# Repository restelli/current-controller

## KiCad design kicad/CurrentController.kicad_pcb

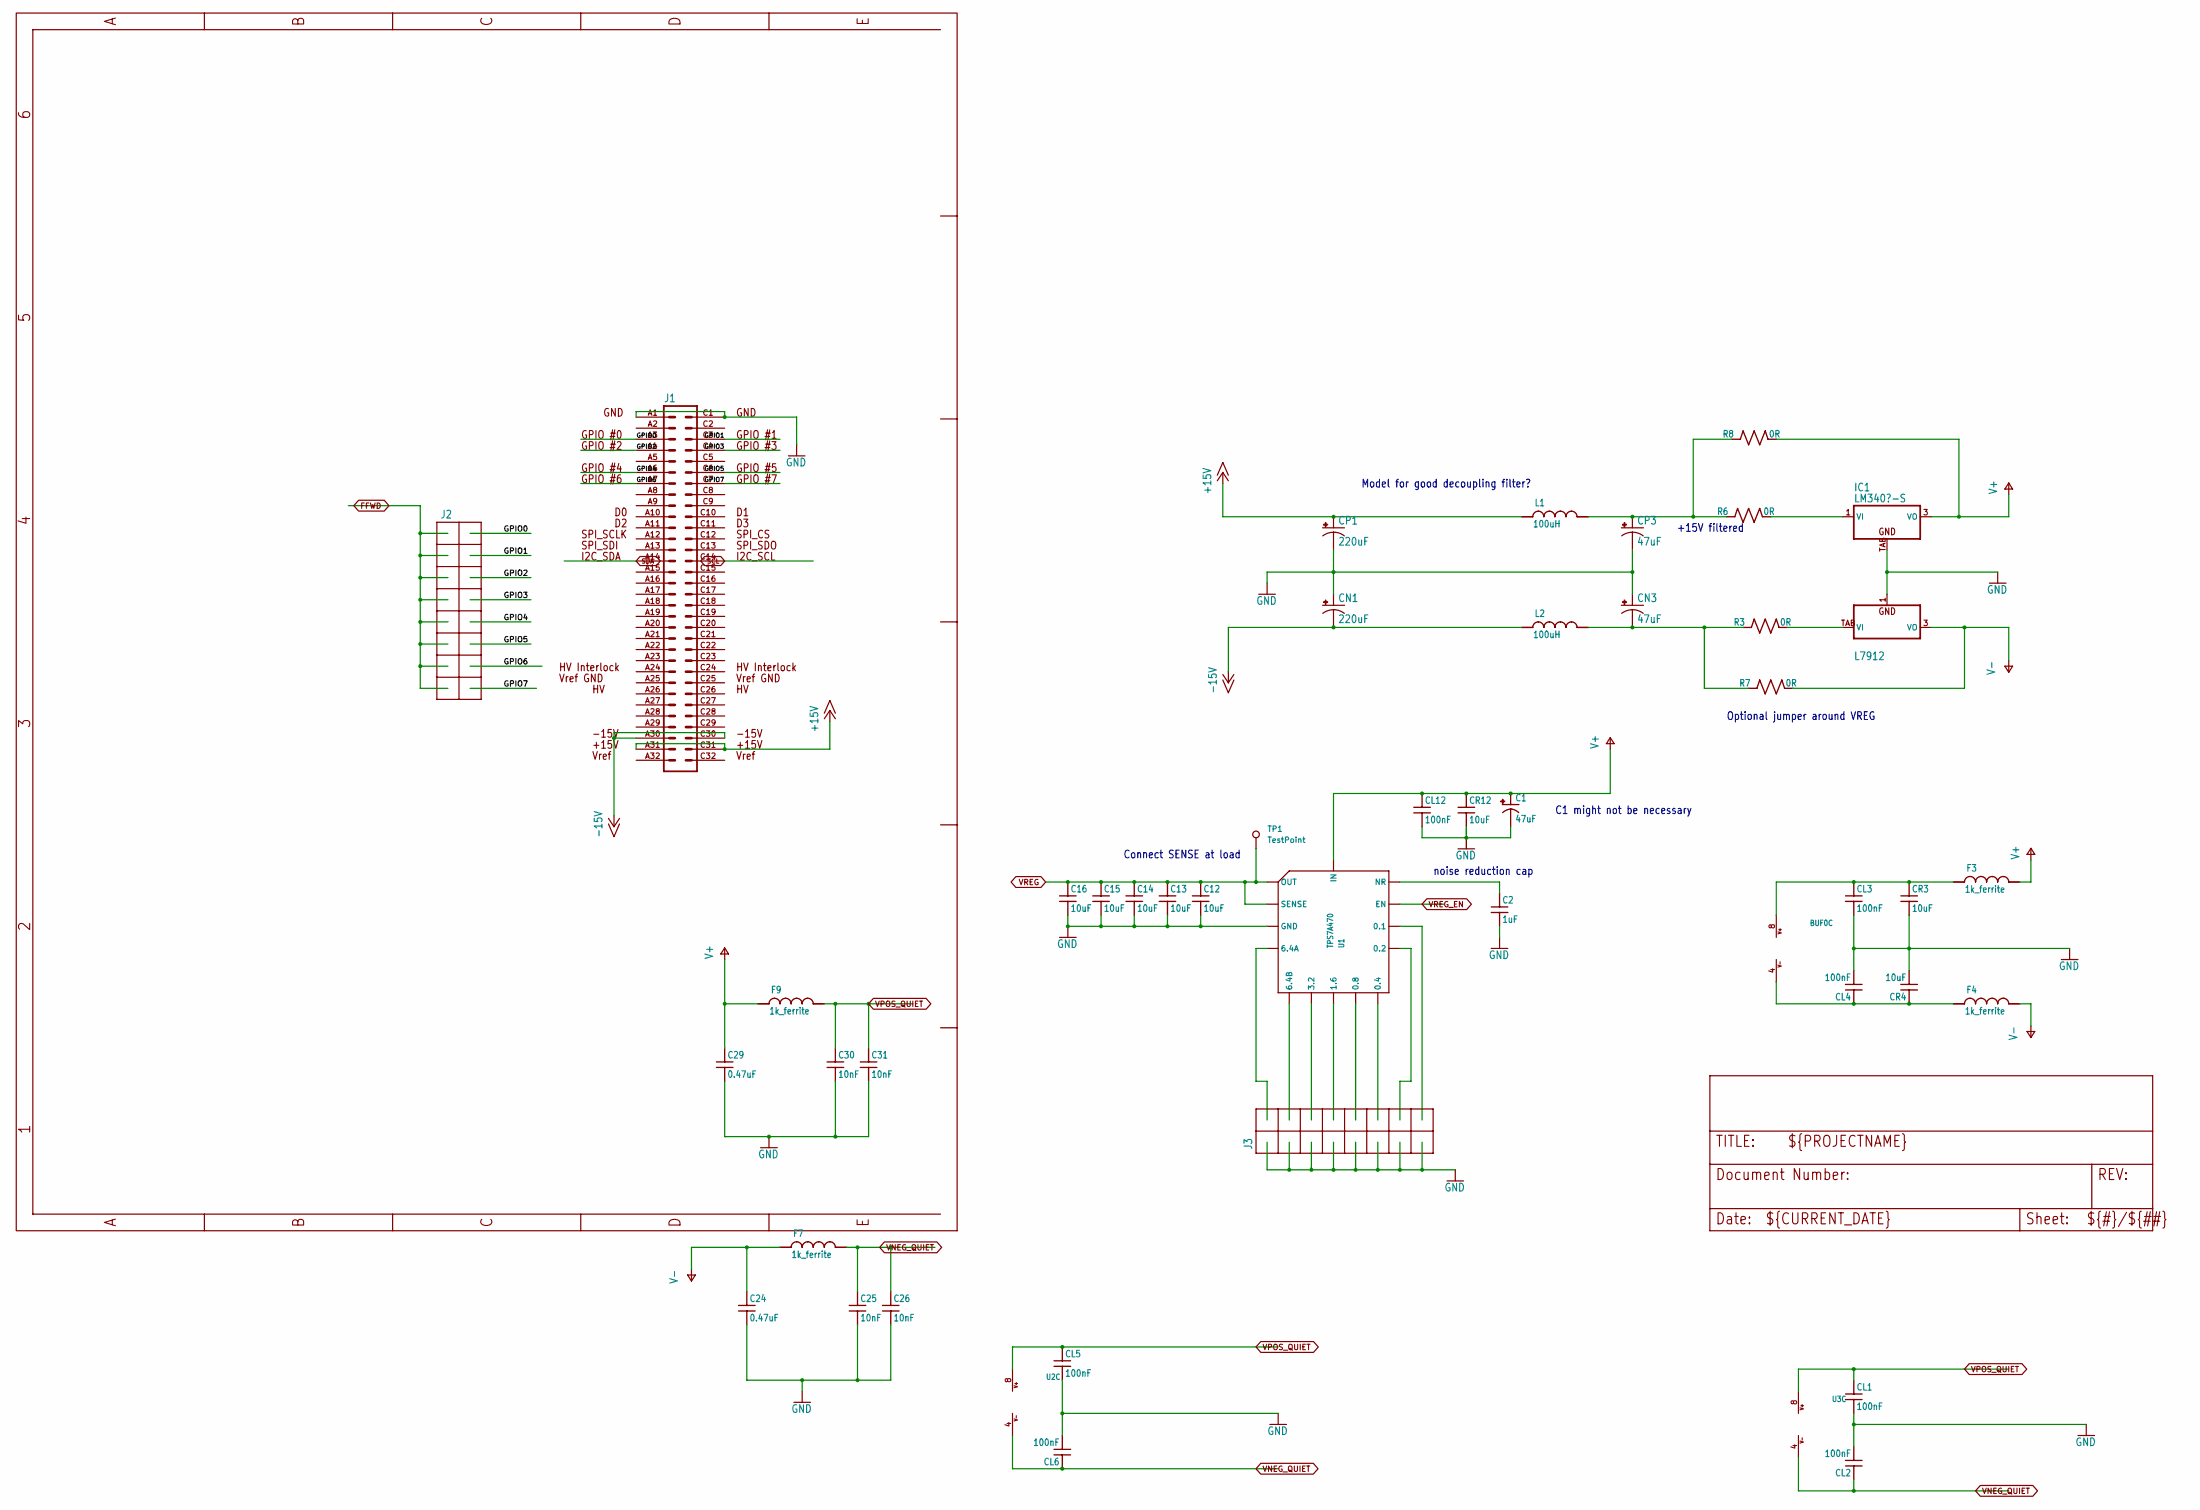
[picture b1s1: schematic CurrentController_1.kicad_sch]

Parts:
BUF0: AD8676; MSOP08; PARTNO AD8676ARMZ
C1: 47uF; C_POL_1206
C2: 1uF; C_MLCC_0603; PARTNO CL10B105KA8NNNC
C12, C13, C14, C15, C16: 10uF; C_MLCC_0805; PARTNO CL21A106KAFN3NE
C24, C29: 0.47uF; C_MLCC_0612; PARTNO LLL31MR71E474MA01L
C25, C26, C30, C31: 10nF; C_MLCC_0306; PARTNO 03063C103KAT2A
CL1, CL2, CL3, CL4, CL5, CL6, CL12: 100nF; C_MLCC_0603; PARTNO C1608X7R1E104K080AA
CN1: 220uF; PANASONIC_F; PARTNO EEE-1VA221UP
CN3: 47uF; CT7343; PARTNO T491D476M025AT
CP1: 220uF; PANASONIC_F; PARTNO EEE-1VA221UP
CP3: 47uF; CT7343; PARTNO T491D476M025AT
CR3, CR4, CR12: 10uF; C_MLCC_0805; PARTNO CL21A106KAFN3NE
F3, F4, F7, F9: 1k_ferrite; L_FERRITE_0603; PARTNO BLM18HG102SN1D
IC1: LM340?-S; TO263-3; PARTNO LM340S-12/NOPB
IC2: L7912; TO223-3; PARTNO MC7912CD2TG
J1: VG64C; VG64-CUTOUT; PARTNO 5650945-5
J2, J3: 2X8_LOW_PROFILE_JUMPER; 2X8_LOW_PROFILE_JUMPER_MATRIX; PARTNO A3B-16PA-2DSA(71)
L1, L2: 100uH; WURTH_1280; PARTNO 74477020
R3, R6, R7, R8: 0R; R_1206; PARTNO ERJ-8GEY0R00V
TP1: TestPoint; TestPoint_Pad_1.0x1.0mm
U1: TPS7A470; S-PVQFN-N20; PARTNO TPS7A4701RGWT
U2, U3: AD8676; MSOP08; PARTNO AD8676ARMZ

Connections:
+15V: CP1.+, J1.A31, J1.C31, L1.P$1 (1)
-15V: CN1.-, J1.A30, J1.C30, L2.P$1 (1)
/CurrentController_1/GPIO0: J1.A3, J2.P$2
/CurrentController_1/GPIO1: J1.C3, J2.P$4
/CurrentController_1/GPIO2: J1.A4, J2.P$6
/CurrentController_1/GPIO3: J1.C4, J2.P$8
/CurrentController_1/GPIO4: J1.A6, J2.P$10
/CurrentController_1/GPIO5: J1.C6, J2.P$12
/CurrentController_1/GPIO6: J1.A7, J2.P$14
/CurrentController_1/GPIO7: J1.C7, J2.P$16
FFWD: J2.P$1, J2.P$3, J2.P$5, J2.P$7, J2.P$9, J2.P$11, J2.P$13, J2.P$15; also elsewhere on the board
GND: C1.P$2 (-), C2.P$2 (2), C12.P$2 (2), C13.P$2 (2), C14.P$2 (2), C15.P$2 (2), C16.P$2 (2), C24.P$2 (2), C25.P$2 (2), C26.P$2 (2), C29.P$2 (2), C30.P$2 (2), C31.P$2 (2), CL1.P$2 (2), CL2.P$2 (2), CL3.P$2 (2), CL4.P$2 (2), CL5.P$2 (2), CL6.P$2 (2), CL12.P$2 (2), CN1.+, CN3.+, CP1.-, CP3.-, CR3.P$2 (2), CR4.P$2 (2), CR12.P$2 (2), IC1.TAB (GND), IC2.1 (GND), J1.A1, J1.C1, J3.P$1, J3.P$3, J3.P$5, J3.P$7, J3.P$9, J3.P$11, J3.P$13, J3.P$15, U1.2 (GND), U1.7 (GND), U1.17 (GND), U1.18 (GND), U1.19 (GND), U1.EXP (GND); also elsewhere on the board
unnamed: BUF0.8 (V+), CL3.P$1 (1), CR3.P$1 (1), F3.P$1 (1)
unnamed: BUF0.4 (V-), CL4.P$1 (1), CR4.P$1 (1), F4.P$1 (1)
unnamed: C2.P$1 (1), U1.14 (NR)
unnamed: IC1.1 (VI), R6.P$2 (2)
unnamed: IC2.TAB (VI), R3.P$2 (2)
unnamed: CP3.+, L1.P$2 (2), R6.P$1 (1), R8.P$1 (1)
unnamed: CN3.-, L2.P$2 (2), R3.P$1 (1), R7.P$1 (1)
unnamed: J3.P$16, U1.12 (0.1)
unnamed: J3.P$14, U1.11 (0.2)
unnamed: J3.P$12, U1.10 (0.4)
unnamed: J3.P$10, U1.9 (0.8)
unnamed: J3.P$8, U1.8 (1.6)
unnamed: J3.P$6, U1.6 (3.2)
unnamed: J3.P$2, U1.4 (6.4A)
unnamed: J3.P$4, U1.5 (6.4B)
SCL: J1.C14; also elsewhere on the board
SDA: J1.A14; also elsewhere on the board
V+: C1.P$1 (+), C29.P$1 (1), CL12.P$1 (1), CR12.P$1 (1), F3.P$2 (2), F9.P$1 (1), IC1.3 (VO), R8.P$2 (2), U1.15 (IN), U1.16 (IN); also elsewhere on the board
V-: C24.P$1 (1), F4.P$2 (2), F7.P$1 (1), IC2.3 (VO), R7.P$2 (2); also elsewhere on the board
VNEG_QUIET: C25.P$1 (1), C26.P$1 (1), CL2.P$1 (1), CL6.P$1 (1), F7.P$2 (2), U2.4 (V-), U3.4 (V-); also elsewhere on the board
VPOS_QUIET: C30.P$1 (1), C31.P$1 (1), CL1.P$1 (1), CL5.P$1 (1), F9.P$2 (2), U2.8 (V+), U3.8 (V+); also elsewhere on the board
VREG: C12.P$1 (1), C13.P$1 (1), C14.P$1 (1), C15.P$1 (1), C16.P$1 (1), TP1.1, U1.1 (OUT), U1.3 (SENSE), U1.20 (OUT); also elsewhere on the board
VREG_EN: U1.13 (EN); also elsewhere on the board

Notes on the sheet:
Optional jumper around VREG
C1 might not be necessary
Model for good decoupling filter?
+15V filtered
Connect SENSE at load
noise reduction cap

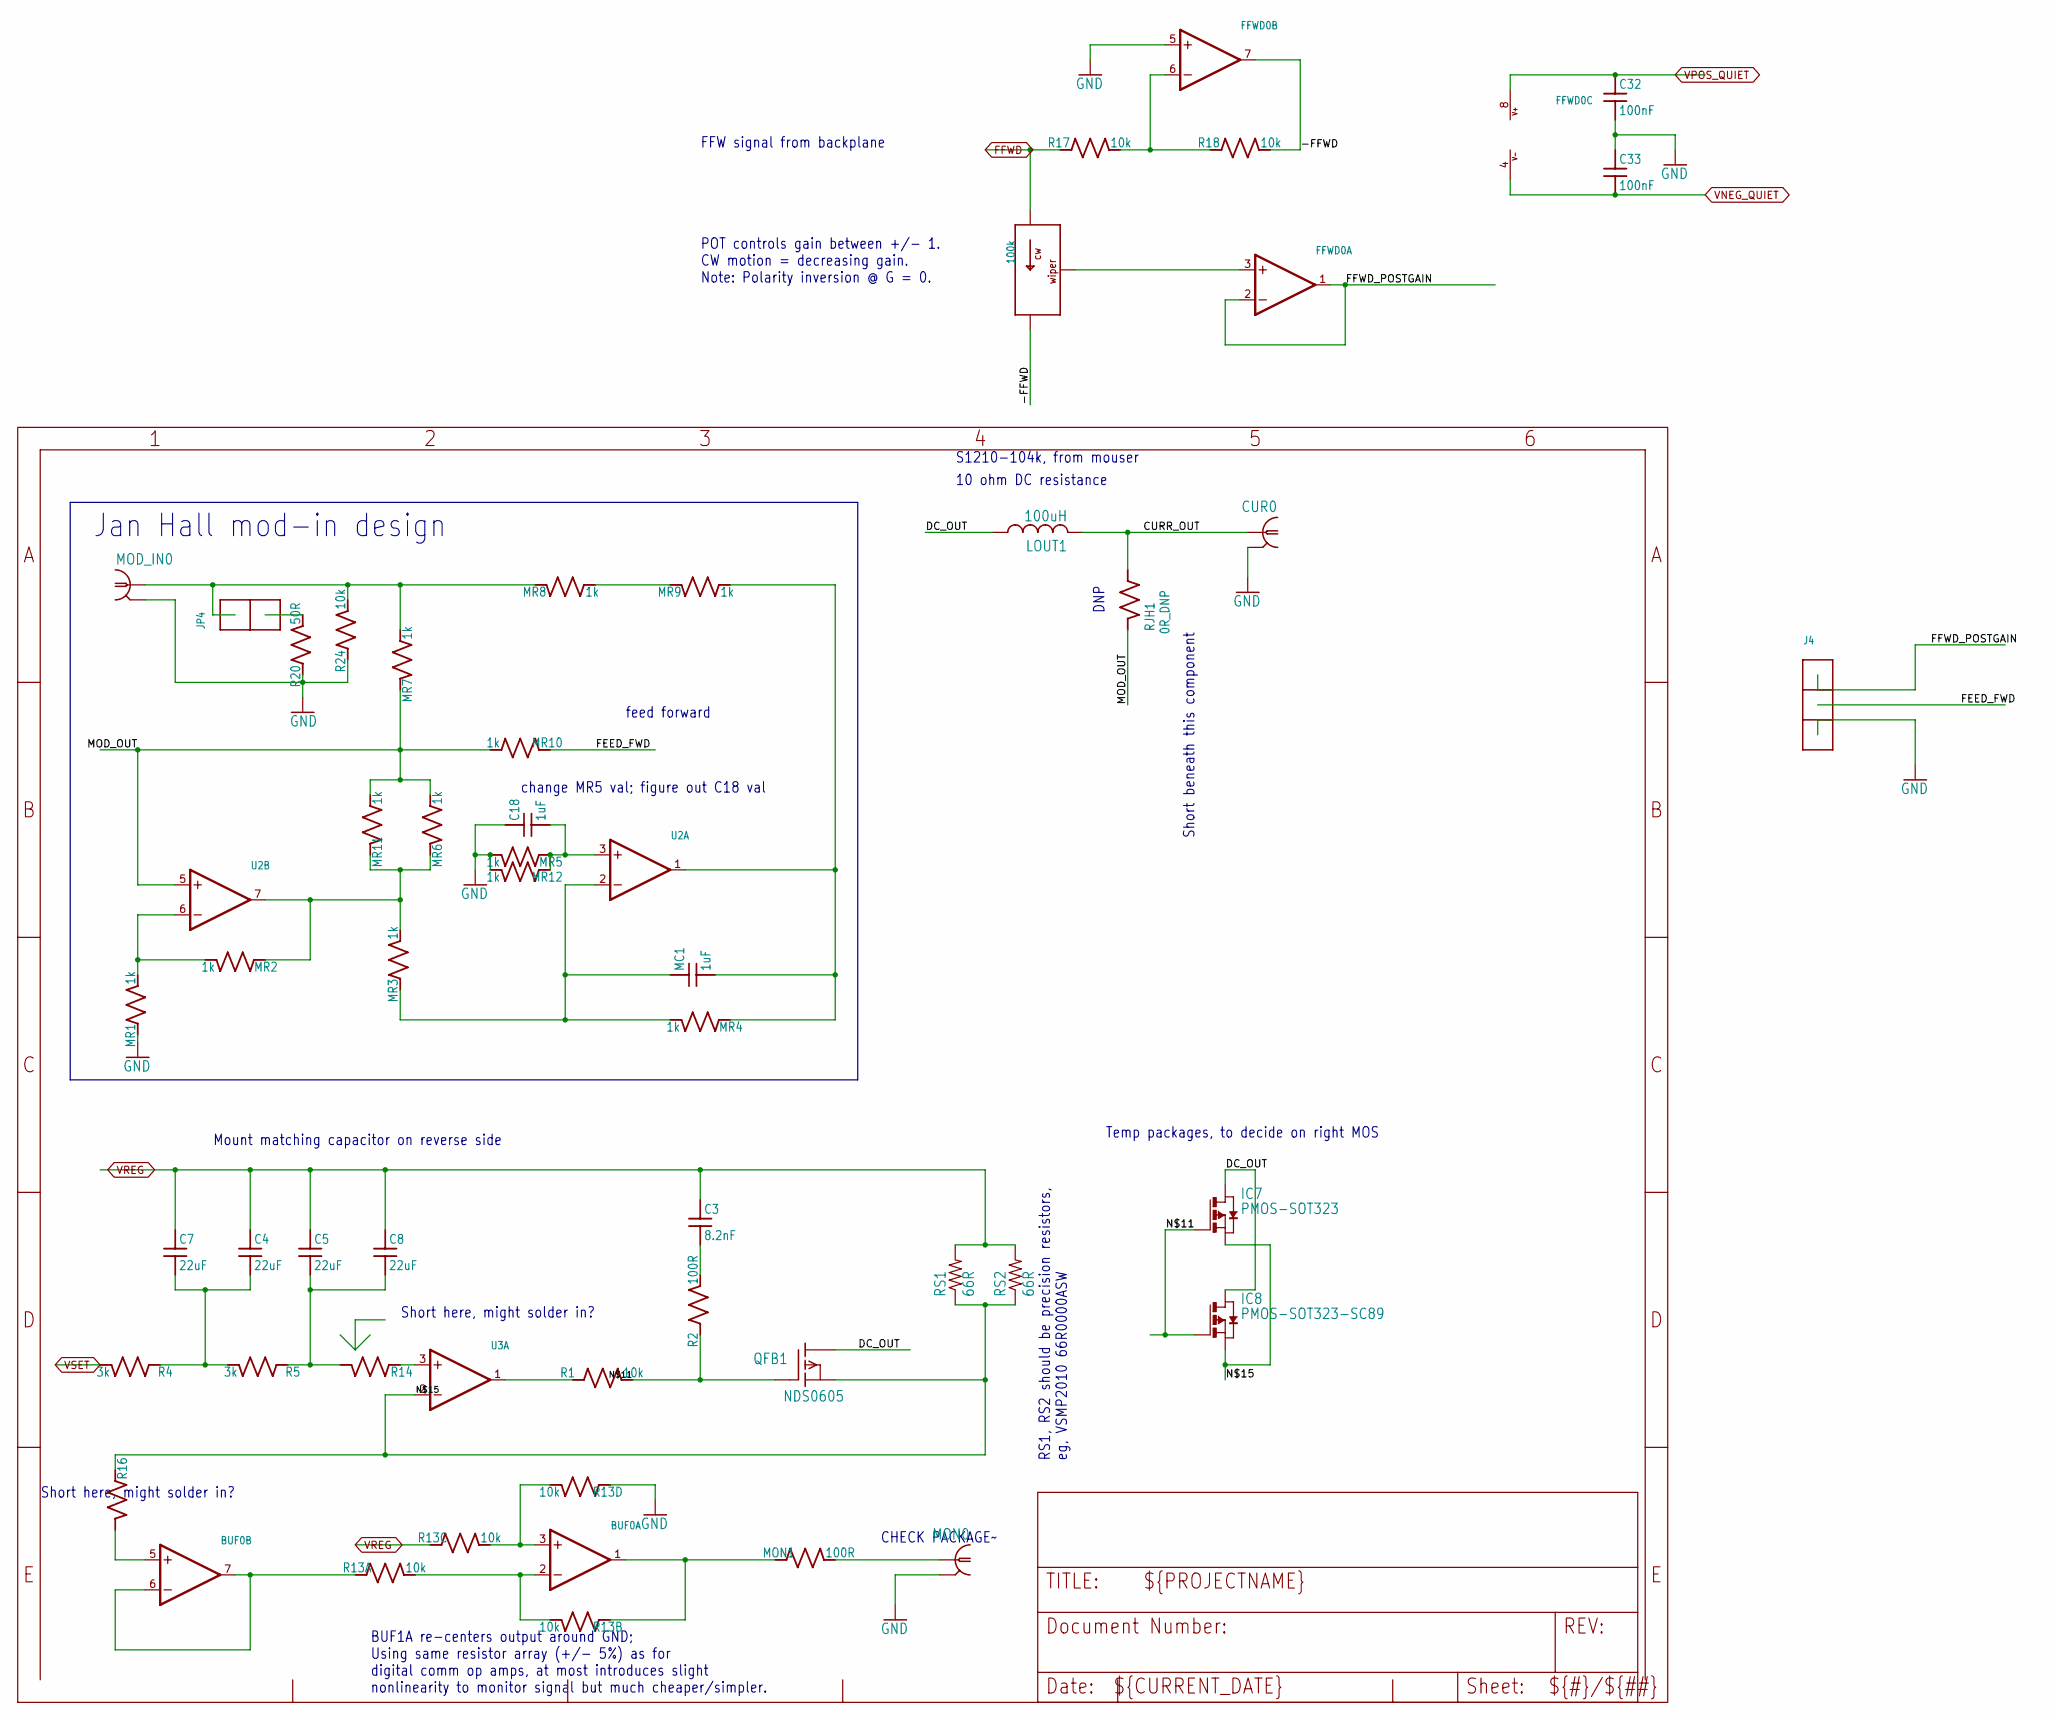
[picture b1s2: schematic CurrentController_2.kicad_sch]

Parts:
BUF0: AD8676; MSOP08; PARTNO AD8676ARMZ
C3: 8.2nF; C_MLCC_0603; PARTNO CL10B822KB8NNNC
C4, C5, C7, C8: 22uF; C_MLCC_0805; PARTNO C2012X5R1E226M125AC
C18: 1uF; C_MLCC_0603; PARTNO CL10B105KA8NNNC
C32, C33: 100nF; C_MLCC_0603; PARTNO C1608X7R1E104K080AA
CUR0: BNC-H; BNC90; PARTNO 5227161-7
FFWD0: AD8676; MSOP08; PARTNO AD8676ARMZ
IC7: PMOS-SOT323; SOT323
IC8: PMOS-SOT323-SC89; SC-89
J4: 1X3_LOW_PROFILE_JUMPER; 1X3_LOW_PROFILE; PARTNO NRPN031PAEN-RC
JP4: 1X2_LOW_PROFILE_JUMPER; 1X2_LOW_PROFILE; PARTNO NRPN021PAEN-RC
LOUT1: 100uH; L3225P; PARTNO CBC3225T680KR
MC1: 1uF; C_MLCC_0603; PARTNO CL10B105KA8NNNC
MOD_IN0: BNC-H; BNC90; PARTNO 5227161-7
MON0: UMC; PARTNO 1909763-1
MON1: 100R; R_0603; PARTNO ERJ-3EKF1000V
MR1, MR2, MR3, MR4, MR5, MR6, MR7, MR8, MR9, MR10, MR11, MR12: 1k; R_0805; PARTNO ERA-6ARB102V
QFB1: NDS0605; SOT-23; PARTNO *
R1, R17, R18, R24: 10k; R_0603; PARTNO ERJ-3EKF1002V
R2: 100R; R_0603; PARTNO ERJ-3EKF1000V
R4, R5: 3k; R_0603; PARTNO ERJ-3EKF3001V
R13: 10k; 742_ARRAY; PARTNO 742C083103JP
R14, R16: R_SMDR0603; R_0603
R20: 50R; R_0805; PARTNO ERJ-6ENF49R9V
RJH1: 0R_DNP; R_0603
RS1, RS2: 66R; R2010
T1: 100k; 3006P; PARTNO 3006P-1-104LF
U2, U3: AD8676; MSOP08; PARTNO AD8676ARMZ

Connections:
/CurrentController_2/-FFWD: FFWD0.7 (OUT), R18.P$2 (2), T1.P$3
/CurrentController_2/CURR_OUT: CUR0.1, LOUT1.2, RJH1.P$1 (1)
/CurrentController_2/DC_OUT: IC7.3 (D), IC8.P$3 (D), LOUT1.1, QFB1.3 (D)
/CurrentController_2/FEED_FWD: J4.P2, MR10.P$1 (1)
/CurrentController_2/FFWD_POSTGAIN: FFWD0.1 (OUT), FFWD0.2 (-IN), J4.P1
/CurrentController_2/MOD_OUT: MR6.P$2 (2), MR7.P$1 (1), MR10.P$2 (2), MR11.P$2 (2), RJH1.P$2 (2), U2.5 (+IN)
/CurrentController_2/N$11: IC7.1 (G), IC8.P$1 (G), QFB1.1 (G), R1.P$2 (2), R2.P$1 (1)
/CurrentController_2/N$15: IC7.2 (S), IC8.P$2 (S), QFB1.2 (S), R16.P$1 (1), RS1.1, RS2.1, U3.2 (-IN)
FFWD: R17.P$1 (1), T1.P$1; also elsewhere on the board
GND: C18.P$1 (1), C32.P$2 (2), C33.P$1 (1), CUR0.2, FFWD0.5 (+IN), J4.P3, MOD_IN0.2, MON0.P$2 (2), MON0.P$3 (2), MR1.P$1 (1), MR5.P$2 (2), MR12.P$2 (2), R13.P$7 (1), R20.P$1 (1), R24.P$1 (1); also elsewhere on the board
unnamed: BUF0.3 (+IN), R13.P$6 (2), R13.P$8 (2)
unnamed: BUF0.2 (-IN), R13.P$2 (2), R13.P$4 (2)
unnamed: BUF0.1 (OUT), MON1.P$1 (1), R13.P$3 (1)
unnamed: BUF0.5 (+IN), R16.P$2 (2)
unnamed: BUF0.6 (-IN), BUF0.7 (OUT), R13.P$1 (1)
unnamed: C3.P$2 (2), R2.P$2 (2)
unnamed: C4.P$2 (2), C7.P$2 (2), R4.P$1 (1), R5.P$2 (2)
unnamed: C5.P$2 (2), C8.P$2 (2), R5.P$1 (1), R14.P$2 (2)
unnamed: C18.P$2 (2), MR5.P$1 (1), MR12.P$1 (1), U2.3 (+IN)
unnamed: FFWD0.3 (+IN), T1.P$2
unnamed: FFWD0.6 (-IN), R17.P$2 (2), R18.P$1 (1)
unnamed: JP4.1, MOD_IN0.1, MR7.P$2 (2), MR8.P$1 (1), R24.P$2 (2)
unnamed: JP4.2, R20.P$2 (2)
unnamed: MC1.P$1 (1), MR3.P$1 (1), MR4.P$2 (2), U2.2 (-IN)
unnamed: MC1.P$2 (2), MR4.P$1 (1), MR9.P$2 (2), U2.1 (OUT)
unnamed: MON0.P$1 (1), MON1.P$2 (2)
unnamed: MR1.P$2 (2), MR2.P$2 (2), U2.6 (-IN)
unnamed: MR8.P$2 (2), MR9.P$1 (1)
unnamed: MR2.P$1 (1), MR3.P$2 (2), MR6.P$1 (1), MR11.P$1 (1), U2.7 (OUT)
unnamed: R1.P$1 (1), U3.1 (OUT)
unnamed: R14.P$1 (1), U3.3 (+IN)
VNEG_QUIET: C33.P$2 (2), FFWD0.4 (V-); also elsewhere on the board
VPOS_QUIET: C32.P$1 (1), FFWD0.8 (V+); also elsewhere on the board
VREG: C3.P$1 (1), C4.P$1 (1), C5.P$1 (1), C7.P$1 (1), C8.P$1 (1), R13.P$5 (1), RS1.2, RS2.2; also elsewhere on the board
VSET: R4.P$2 (2); also elsewhere on the board

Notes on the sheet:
change MR5 val; figure out C18 val
CHECK PACKAGE~
S1210-104k, from mouser
Jan Hall mod-in design
Short beneath this component
POT controls gain between +/- 1. CW motion = decreasing gain. Note: Polarity inversion @ G = 0.
FFW signal from backplane
10 ohm DC resistance
DNP
RS1, RS2 should be precision resistors, eg, VSMP2010 66R0000ASW
feed forward
Short here, might solder in?
Mount matching capacitor on reverse side
Temp packages, to decide on right MOS
BUF1A re-centers output around GND; Using same resistor array (+/- 5%) as for digital comm op amps, at most introduces slight nonlinearity to monitor signal but much cheaper/simpler.

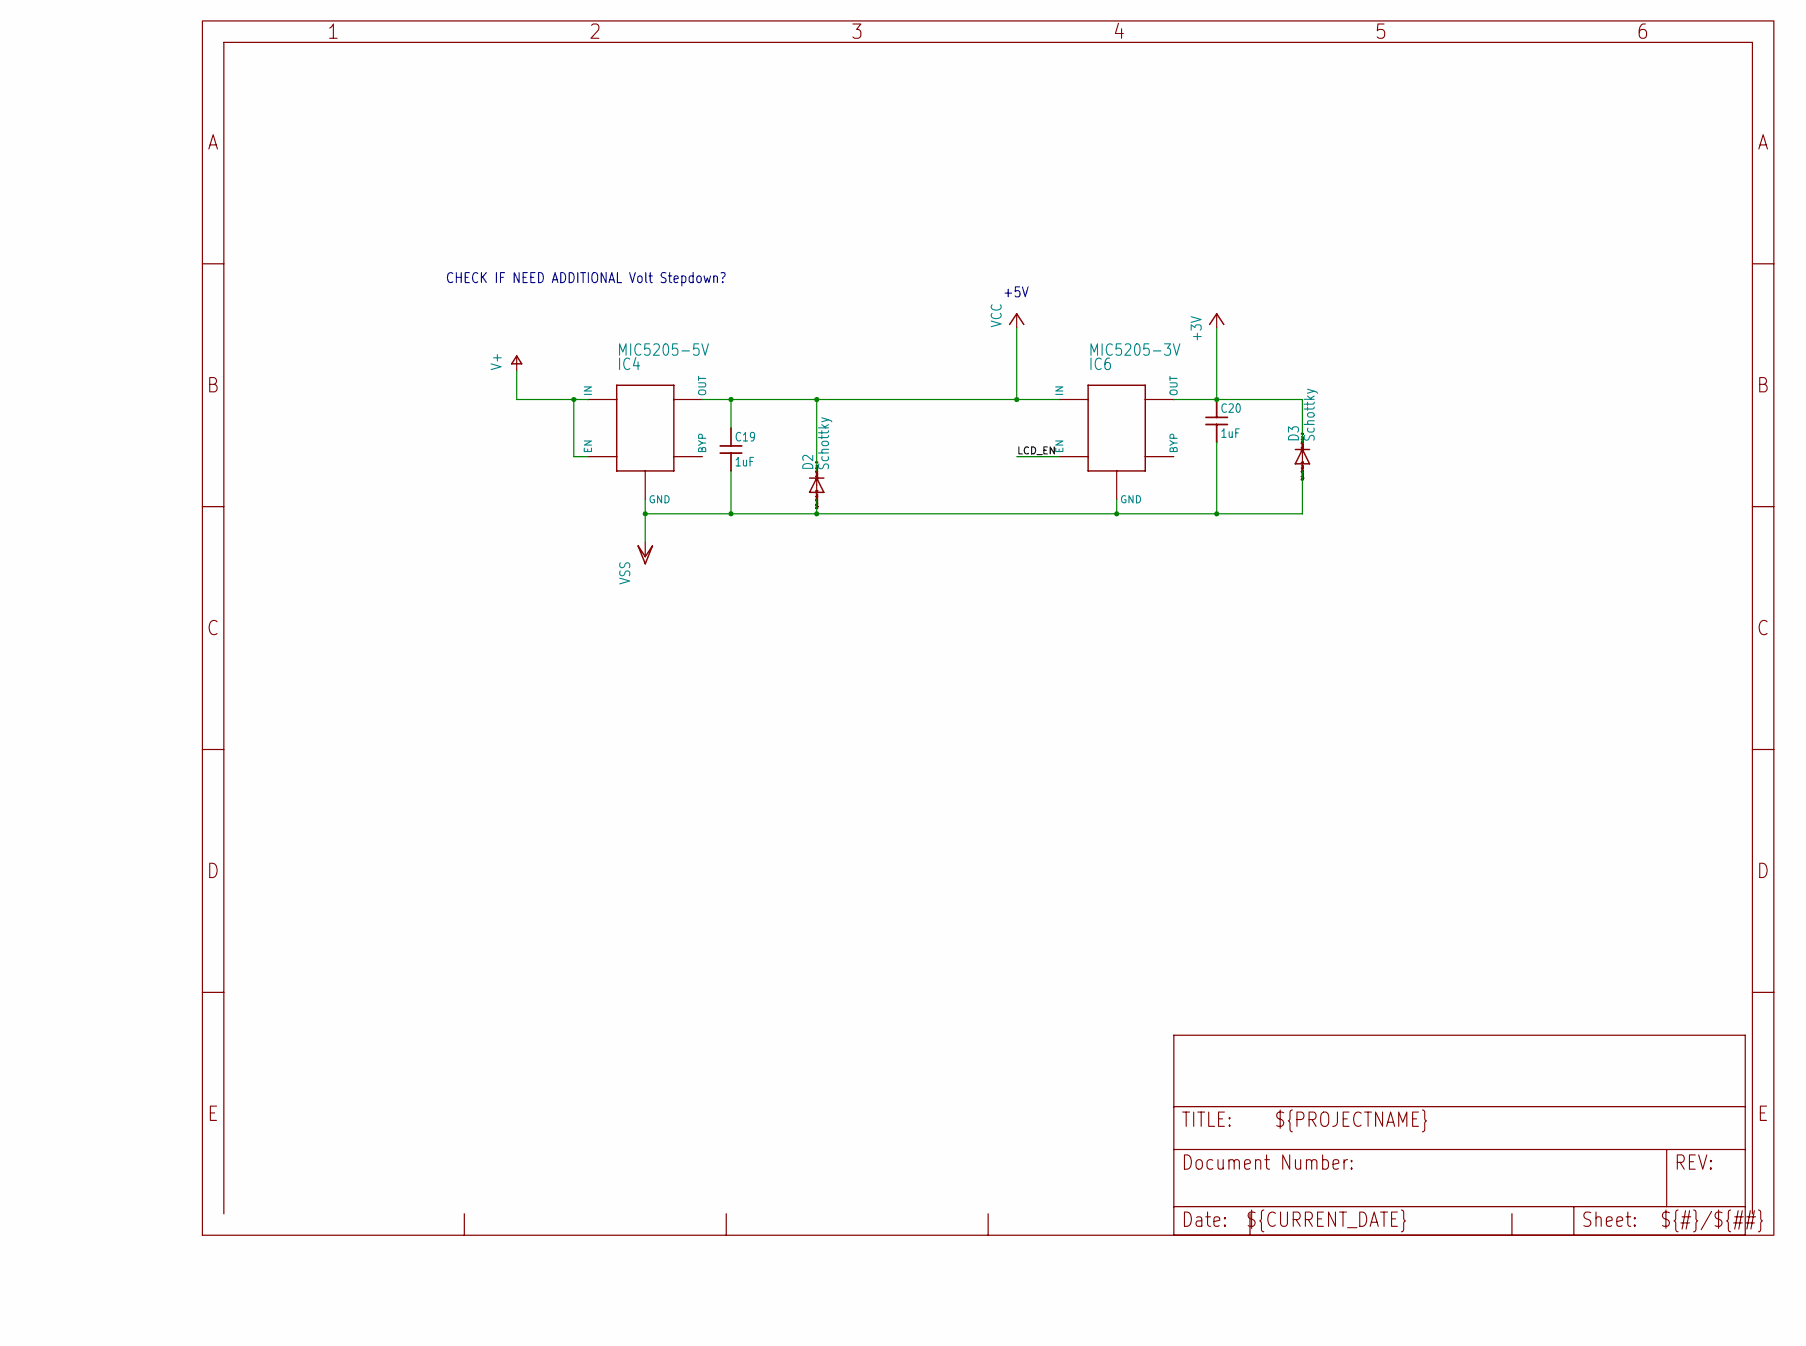
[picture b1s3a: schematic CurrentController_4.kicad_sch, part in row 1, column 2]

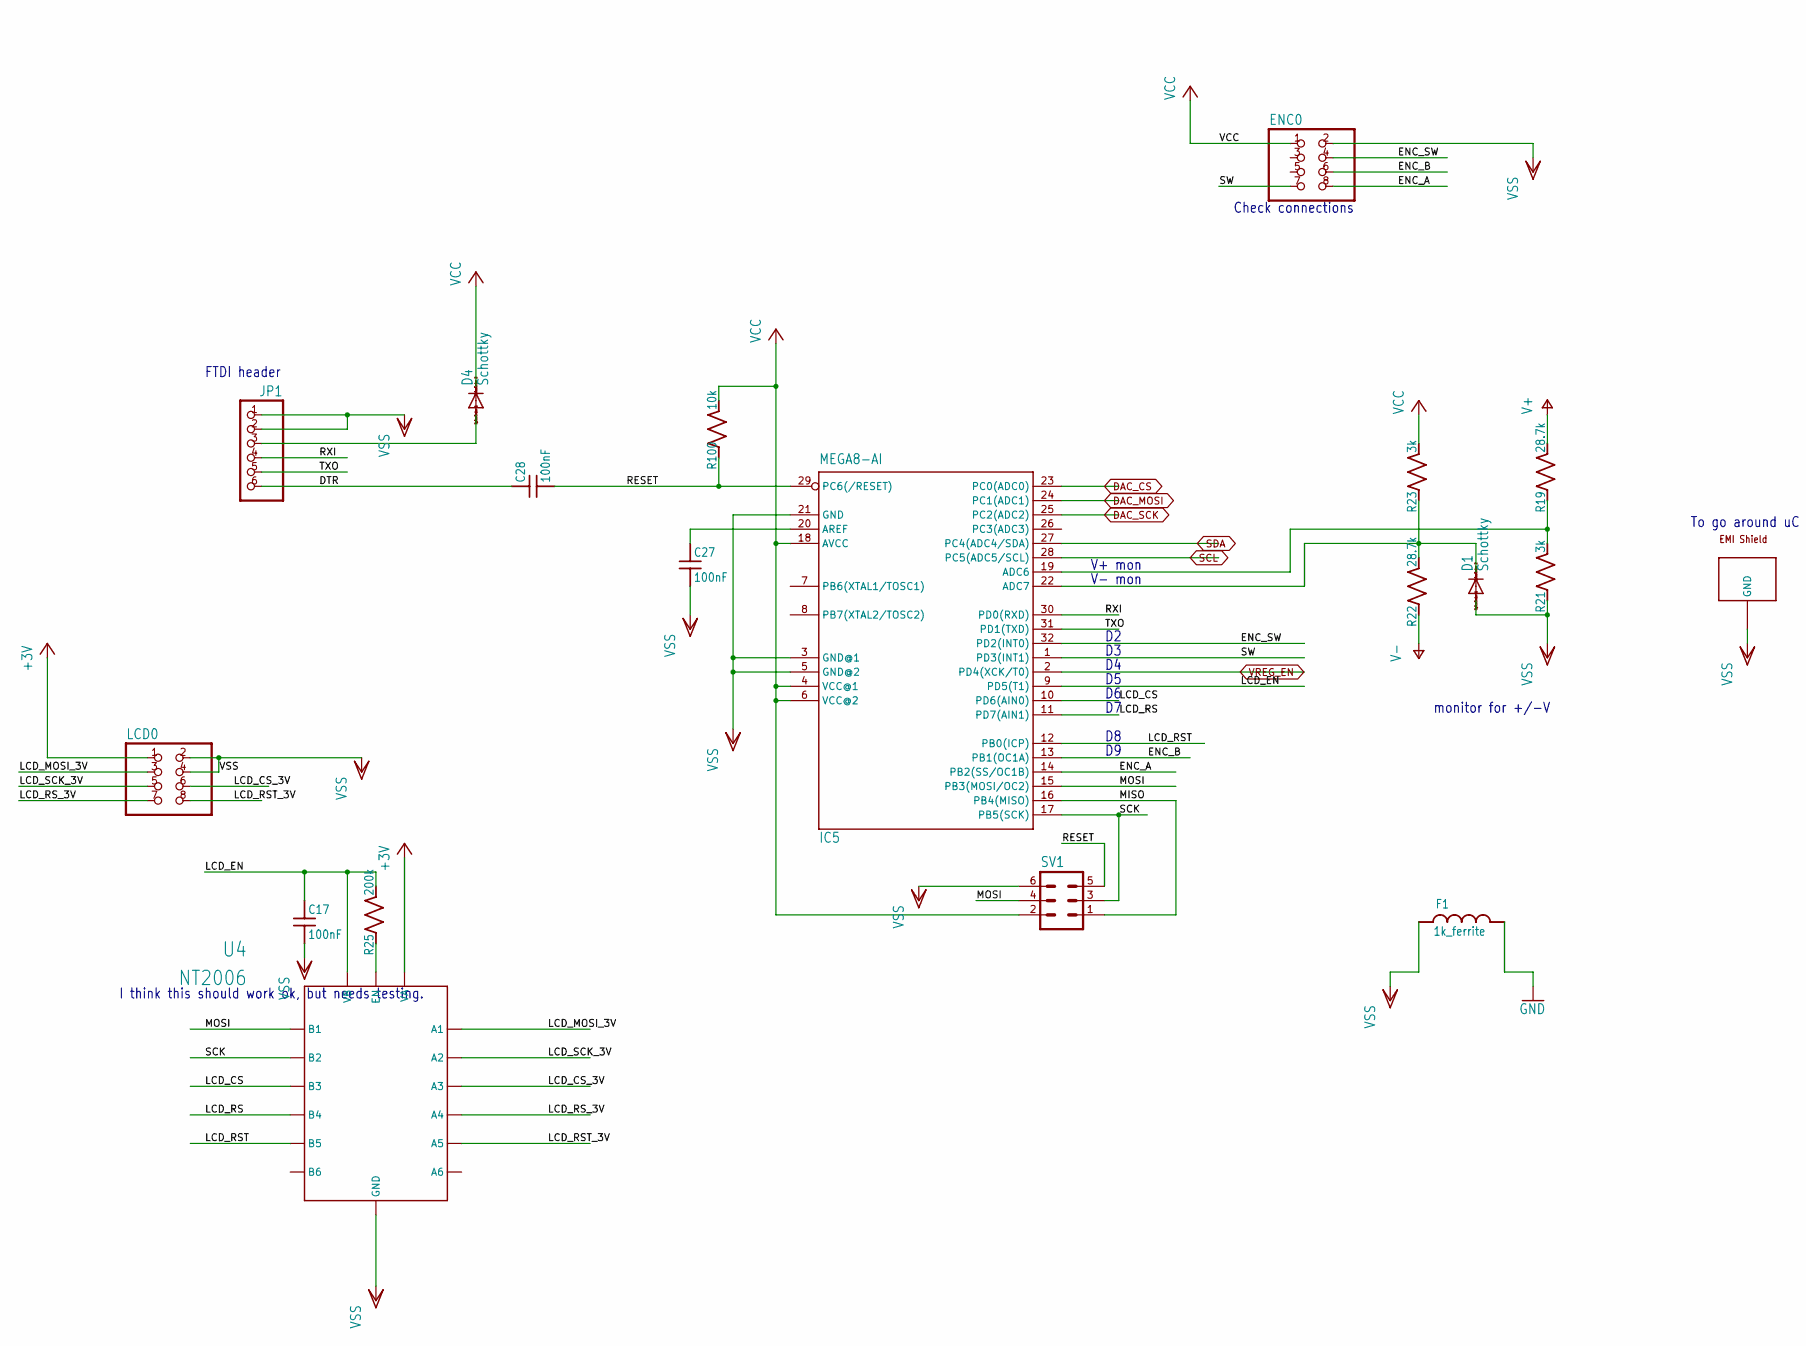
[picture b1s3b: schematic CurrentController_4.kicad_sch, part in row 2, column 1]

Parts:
C17, C27, C28: 100nF; C_MLCC_0603; PARTNO C1608X7R1E104K080AA
C19, C20: 1uF; C_MLCC_0603; PARTNO CL10B105KA8NNNC
D1, D2, D3, D4: Schottky; SOD523; PARTNO PMEG3005EB,115
ENC0: PINHD-2X4-SHROUD; ML08; PARTNO 75869-132LF
F1: 1k_ferrite; L_FERRITE_0603; PARTNO BLM18HG102SN1D
IC4: MIC5205-5V; SOT23-5L; PARTNO MIC5205-5.0YM5-TR
IC5: MEGA8-AI; TQFP32-08; PARTNO ATMEGA328P-AU
IC6: MIC5205-3V; SOT23-5L; PARTNO MIC5205-3.0YM5-TR
JP1: PINHD-1X6; 1X06; PARTNO 68000-406HLF
LCD0: PINHD-2X4-SHROUD; ML08; PARTNO 75869-132LF
R19, R22: 28.7k; R_0603; PARTNO ERJ-3EKF2872V
R21, R23: 3k; R_0603; PARTNO ERJ-3EKF3001V
R25: 200k; R_0603; PARTNO ERJ-3EKF2003V
R100: 10k; R_0603; PARTNO ERJ-3EKF1002V
SV1: MA03-2; PARTNO 67996-406HLF
U4: NT2006; HVQFN16; PARTNO NVT2006BS,118
U$5: WURTH_EMI; WURTH_SHIELD; PARTNO 36103205

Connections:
+3V: C20.P$1 (1), D3.C, IC6.5 (OUT), LCD0.1, U4.16 (VA)
/CurrentController_4/DTR: C28.P$1 (1), JP1.6
/CurrentController_4/ENC_A: ENC0.8, IC5.14 (PB2(SS/OC1B))
/CurrentController_4/ENC_B: ENC0.6, IC5.13 (PB1(OC1A))
/CurrentController_4/ENC_SW: ENC0.4, IC5.32 (PD2(INT0))
/CurrentController_4/LCD_CS: IC5.10 (PD6(AIN0)), U4.10 (B3)
/CurrentController_4/LCD_CS_3V: LCD0.6, U4.3 (A3)
/CurrentController_4/LCD_EN: C17.P$1 (1), IC5.9 (PD5(T1)), IC6.3 (EN), R25.P$2 (2), U4.13 (VB)
/CurrentController_4/LCD_MOSI_3V: LCD0.3, U4.1 (A1)
/CurrentController_4/LCD_RS: IC5.11 (PD7(AIN1)), U4.9 (B4)
/CurrentController_4/LCD_RST: IC5.12 (PB0(ICP)), U4.8 (B5)
/CurrentController_4/LCD_RST_3V: LCD0.8, U4.5 (A5)
/CurrentController_4/LCD_RS_3V: LCD0.7, U4.4 (A4)
/CurrentController_4/LCD_SCK_3V: LCD0.5, U4.2 (A2)
/CurrentController_4/MISO: IC5.16 (PB4(MISO)), SV1.1
/CurrentController_4/MOSI: IC5.15 (PB3(MOSI/OC2)), SV1.4, U4.12 (B1)
/CurrentController_4/RESET: C28.P$2 (2), IC5.29 (PC6(/RESET)), R100.P$1 (1), SV1.5
/CurrentController_4/RXI: IC5.30 (PD0(RXD)), JP1.4
/CurrentController_4/SCK: IC5.17 (PB5(SCK)), SV1.3, U4.11 (B2)
/CurrentController_4/SW: ENC0.7, IC5.1 (PD3(INT1))
/CurrentController_4/TXO: IC5.31 (PD1(TXD)), JP1.5
DAC_CS: IC5.23 (PC0(ADC0)); also elsewhere on the board
DAC_MOSI: IC5.24 (PC1(ADC1)); also elsewhere on the board
DAC_SCK: IC5.25 (PC2(ADC2)); also elsewhere on the board
GND: F1.P$2 (2); also elsewhere on the board
unnamed: C27.P$1 (1), IC5.20 (AREF)
unnamed: D4.A, JP1.3
unnamed: IC5.19 (ADC6), R19.P$1 (1), R21.P$2 (2)
unnamed: D1.C, IC5.22 (ADC7), R22.P$2 (2), R23.P$1 (1)
unnamed: R25.P$1 (1), U4.14 (EN)
SCL: IC5.28 (PC5(ADC5/SCL)); also elsewhere on the board
SDA: IC5.27 (PC4(ADC4/SDA)); also elsewhere on the board
V+: IC4.1 (IN), IC4.3 (EN), R19.P$2 (2); also elsewhere on the board
V-: R22.P$1 (1); also elsewhere on the board
VCC: C19.P$1 (1), D2.C, D4.C, ENC0.1, IC4.5 (OUT), IC5.4 (VCC@1), IC5.6 (VCC@2), IC5.18 (AVCC), IC6.1 (IN), R23.P$2 (2), R100.P$2 (2), SV1.2
VREG_EN: IC5.2 (PD4(XCK/T0)); also elsewhere on the board
VSS: C17.P$2 (2), C19.P$2 (2), C20.P$2 (2), C27.P$2 (2), D1.A, D2.A, D3.A, ENC0.2, F1.P$1 (1), IC4.2 (GND), IC5.3 (GND@1), IC5.5 (GND@2), IC5.21 (GND), IC6.2 (GND), JP1.1, JP1.2, LCD0.2, LCD0.4, R21.P$1 (1), SV1.6, U4.15 (GND), U4.P$17 (GND), U$5.P$1 (GND), U$5.P$2 (GND), U$5.P$3 (GND), U$5.P$4 (GND), U$5.P$5 (GND), U$5.P$6 (GND), U$5.P$7 (GND), U$5.P$8 (GND), U$5.P$9 (GND), U$5.P$10 (GND), U$5.P$11 (GND), U$5.P$12 (GND), U$5.P$13 (GND), U$5.P$14 (GND), U$5.P$15 (GND), U$5.P$16 (GND)

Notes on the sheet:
Check connections
monitor for +/-V
CHECK IF NEED ADDITIONAL Volt Stepdown?
V- mon
To go around uC
+5V
I think this should work ok, but needs testing.
V+ mon
FTDI header

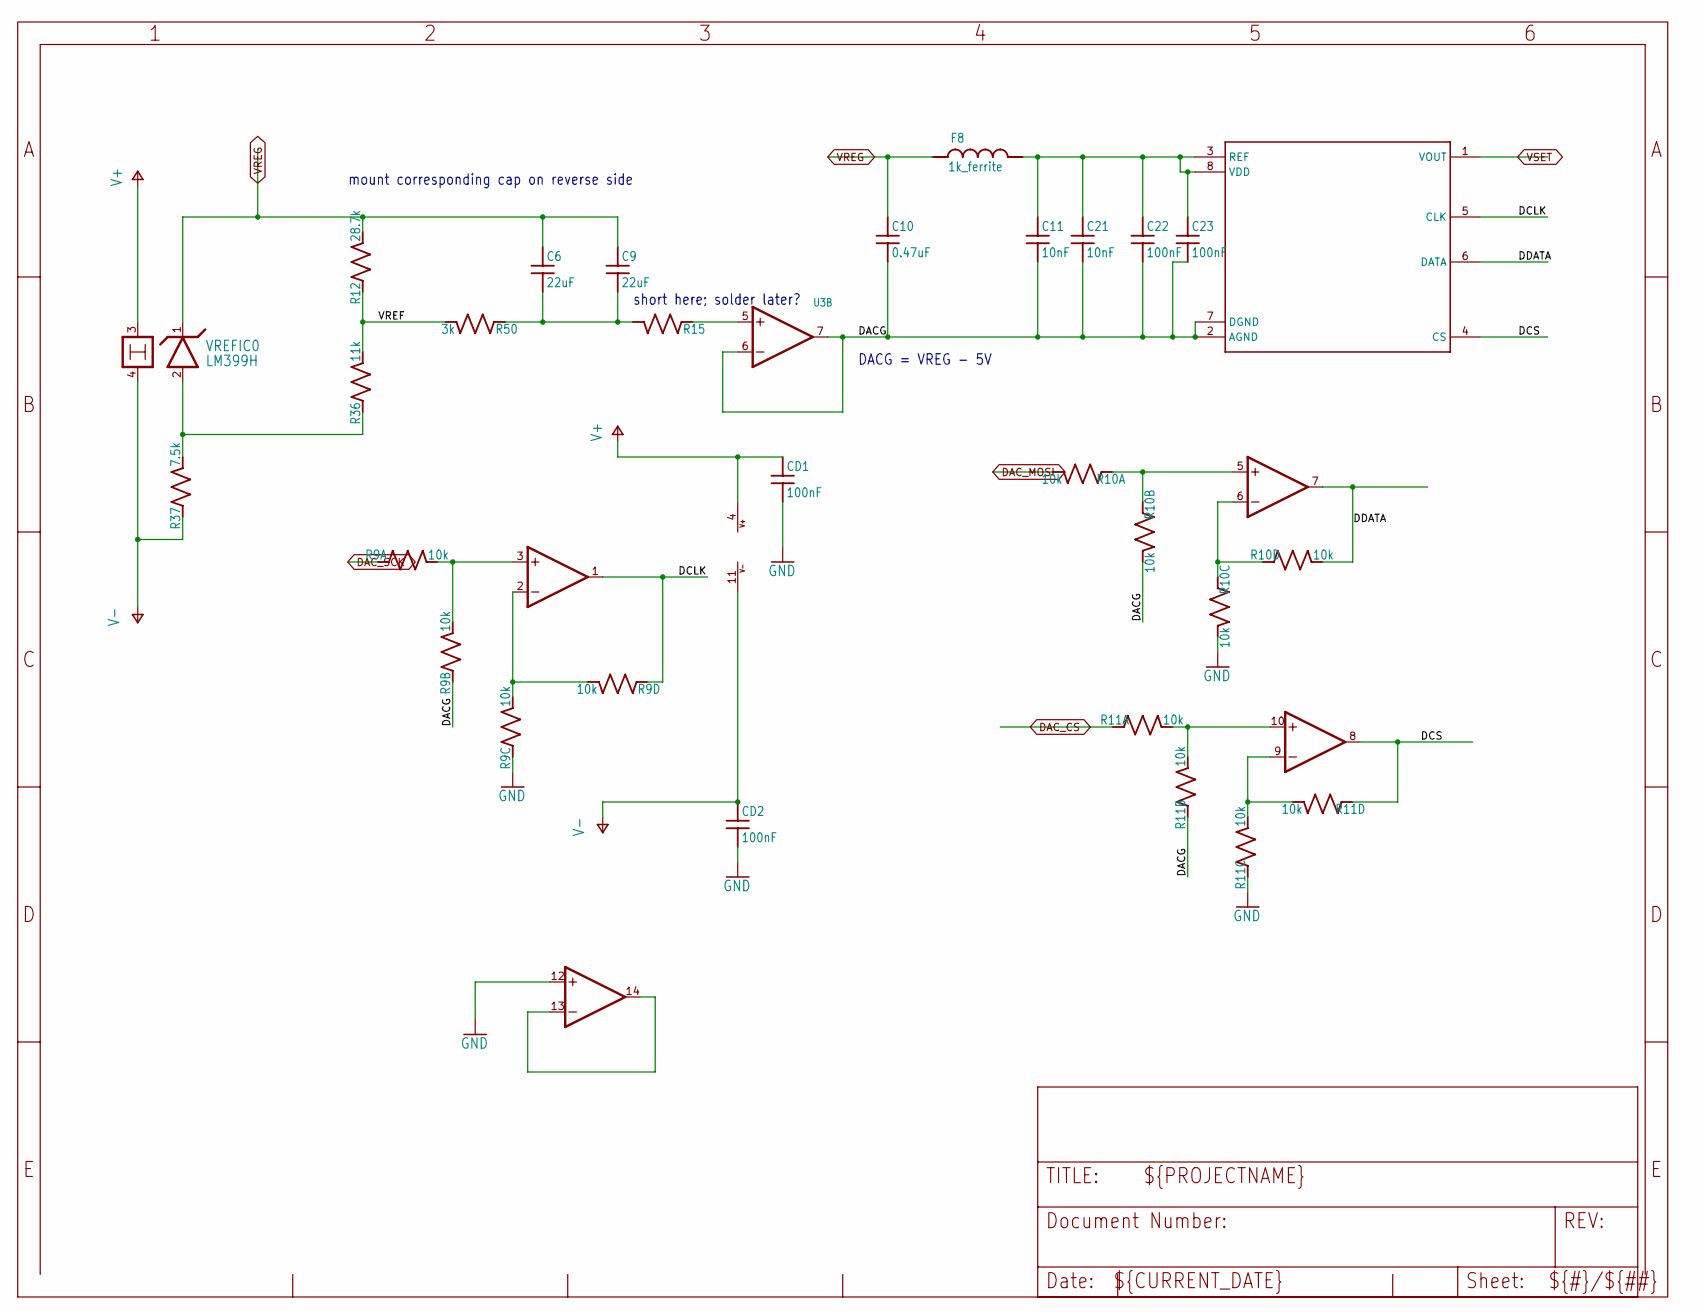
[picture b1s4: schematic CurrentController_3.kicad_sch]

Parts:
C6, C9: 22uF; C_MLCC_0805; PARTNO C2012X5R1E226M125AC
C10: 0.47uF; C_MLCC_0612; PARTNO LLL31MR71E474MA01L
C11, C21: 10nF; C_MLCC_0306; PARTNO 03063C103KAT2A
C22, C23: 100nF; C_MLCC_0603; PARTNO C1608X7R1E104K080AA
CD1, CD2: 100nF; C_MLCC_0603; PARTNO C1608X7R1E104K080AA
DAC1: AD5541; SOIC-8; PARTNO AD5541BRZ
F8: 1k_ferrite; L_FERRITE_0603; PARTNO BLM18HG102SN1D
IC3: TS514; SO14; PARTNO TS514AIDT
R9, R10, R11: 10k; 742_ARRAY; PARTNO 742C083103JP
R12: 28.7k; R_0603; PARTNO ERJ-3EKF2872V
R15: R_SMDR0603; R_0603
R36: 11k; R_0603; PARTNO ERJ-3EKF1102V
R37: 7.5k; R_0603; PARTNO ERJ-3EKF7501V
R50: 3k; R_0603; PARTNO ERJ-3EKF3001V
U3: AD8676; MSOP08; PARTNO AD8676ARMZ
VREFIC0: LM399H; TO39_4; PARTNO LM399H#PBF

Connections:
/CurrentController_3/DACG: C10.P$2 (2), C11.P$2 (2), C21.P$2 (2), C22.P$2 (2), C23.P$2 (2), DAC1.2 (AGND), DAC1.7 (DGND), R9.P$3 (1), R10.P$4 (2), R11.P$3 (1), U3.6 (-IN), U3.7 (OUT)
/CurrentController_3/DCLK: DAC1.5 (CLK), IC3.1 (OUT), R9.P$7 (1)
/CurrentController_3/DCS: DAC1.4 (CS), IC3.8 (OUT), R11.P$7 (1)
/CurrentController_3/DDATA: DAC1.6 (DATA), IC3.7 (OUT), R10.P$8 (2)
/CurrentController_3/VREF: R12.P$1 (1), R36.P$2 (2), R50.P$2 (2)
DAC_CS: R11.P$1 (1); also elsewhere on the board
DAC_MOSI: R10.P$2 (2); also elsewhere on the board
DAC_SCK: R9.P$1 (1); also elsewhere on the board
GND: CD1.P$2 (2), CD2.P$2 (2), IC3.12 (+IN), R9.P$5 (1), R10.P$6 (2), R11.P$5 (1); also elsewhere on the board
unnamed: C6.P$2 (2), C9.P$2 (2), R15.P$2 (2), R50.P$1 (1)
unnamed: C11.P$1 (1), C21.P$1 (1), C22.P$1 (1), C23.P$1 (1), DAC1.3 (REF), DAC1.8 (VDD), F8.P$2 (2)
unnamed: IC3.3 (+IN), R9.P$2 (2), R9.P$4 (2)
unnamed: IC3.2 (-IN), R9.P$6 (2), R9.P$8 (2)
unnamed: IC3.5 (+IN), R10.P$1 (1), R10.P$3 (1)
unnamed: IC3.6 (-IN), R10.P$5 (1), R10.P$7 (1)
unnamed: IC3.10 (+IN), R11.P$2 (2), R11.P$4 (2)
unnamed: IC3.9 (-IN), R11.P$6 (2), R11.P$8 (2)
unnamed: IC3.13 (-IN), IC3.14 (OUT)
unnamed: R15.P$1 (1), U3.5 (+IN)
unnamed: R36.P$1 (1), R37.P$2 (2), VREFIC0.2
V+: CD1.P$1 (1), IC3.4 (V+), VREFIC0.3; also elsewhere on the board
V-: CD2.P$1 (1), IC3.11 (V-), R37.P$1 (1), VREFIC0.4; also elsewhere on the board
VREG: C6.P$1 (1), C9.P$1 (1), C10.P$1 (1), F8.P$1 (1), R12.P$2 (2), VREFIC0.1; also elsewhere on the board
VSET: DAC1.1 (VOUT); also elsewhere on the board

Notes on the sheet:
DACG = VREG - 5V
short here; solder later?
mount corresponding cap on reverse side
